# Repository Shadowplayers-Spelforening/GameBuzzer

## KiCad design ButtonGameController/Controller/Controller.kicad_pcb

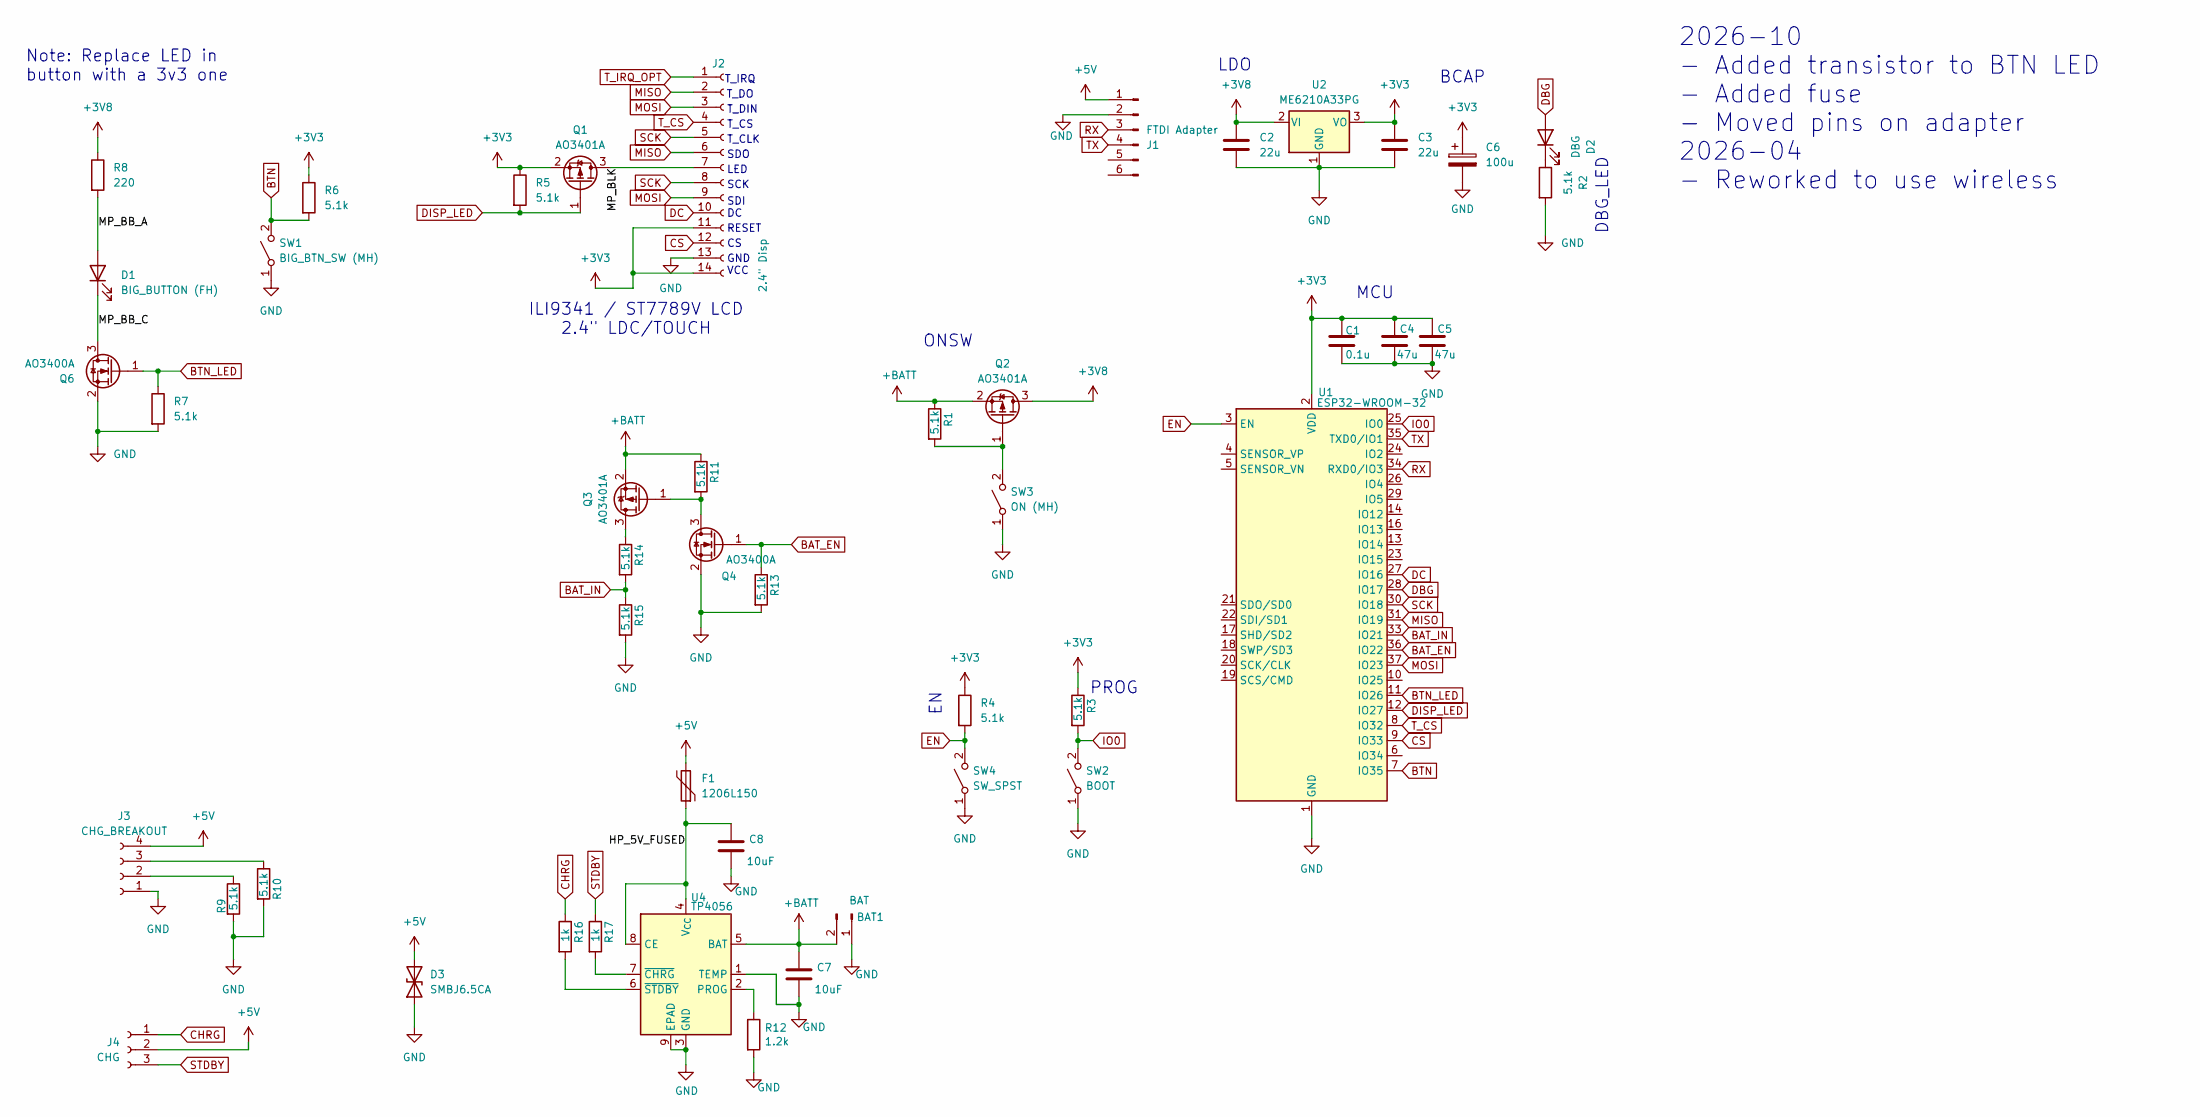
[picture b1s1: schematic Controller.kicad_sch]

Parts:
BAT1: BAT; PinSocket_1x02_P2.54mm_Vertical
C1: 0.1u; C_0603_1608Metric
C2, C3: 22u; C_0805_2012Metric
C4, C5: 47u; C_1206_3216Metric
C6: 100u; CP_Elec_5x5.4
C7, C8: 10uF; C_0805_2012Metric; LCSC C15850
D1: BIG_BUTTON (FH); LED_D5.0mm
D2: DBG; LED_0805_2012Metric
D3: SMBJ6.5CA; D_SMB_Unidirectional
F1: 1206L150; Fuse_1206_3216Metric
J1: FTDI Adapter; PinSocket_1x06_P2.54mm_Horizontal
J2: 2.4" Disp; PinSocket_1x14_P2.54mm_Vertical
J3: CHG_BREAKOUT; JST_PH_B4B-PH-K_1x04_P2.00mm_Vertical
J4: CHG; PinSocket_1x03_P2.54mm_Vertical
Q1, Q2, Q3: AO3401A; SOT-23
Q4, Q6: AO3400A; SOT-23
R1, R2, R3, R4, R5, R6, R7, R9, R10, R11, R13, R14, R15: 5.1k; R_0603_1608Metric
R8: 220; R_0805_2012Metric
R12: 1.2k; R_0603_1608Metric; LCSC C4177
R16, R17: 1k; R_0603_1608Metric
SW1: BIG_BTN_SW (MH); PinSocket_1x02_P2.54mm_Vertical
SW2: BOOT; SW_SPST_CK_RS282G05A3
SW3: ON (MH); PinHeader_1x02_P2.54mm_Vertical
SW4: SW_SPST; SW_SPST_CK_RS282G05A3
U1: ESP32-WROOM-32
U2: ME6210A33PG; SOT-89-3
U4: TP4056; SOIC-8-1EP_3.9x4.9mm_P1.27mm_EP2.41x3.3mm_ThermalVias; LCSC C725790

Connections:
+3V3: C1.1, C3.2, C4.1, C5.1, C6.1, J2.11, J2.14, Q1.2 (S), R3.1, R4.1, R5.1, R6.1, U1.2 (VDD), U2.3 (VO)
+3V8: C2.2, Q2.3 (D), R8.1, U2.2 (VI)
+5V: D3.2 (A2), F1.2, J1.1, J3.4, J4.2
+BATT: BAT1.2, C7.1, Q2.2 (S), Q3.2 (S), R1.1, R11.1, U4.5 (BAT)
/HP_5V_FUSED: C8.1, F1.1, U4.4 (V_{CC}), U4.8 (CE)
/MP_BB_A: D1.2 (A), R8.2
/MP_BB_C: D1.1 (K), Q6.3 (D)
/MP_BLK: J2.7, Q1.3 (D)
BAT_EN: Q4.1 (G), R13.1, U1.36 (IO22)
BAT_IN: R14.2, R15.1, U1.33 (IO21)
BTN: R6.2, SW1.2 (B), U1.7 (IO35)
BTN_LED: Q6.1 (G), R7.1, U1.11 (IO26)
CHRG: J4.1, R16.1
CS: J2.12, U1.9 (IO33)
DBG: D2.2 (A), U1.28 (IO17)
DC: J2.10, U1.27 (IO16)
DISP_LED: Q1.1 (G), R5.2, U1.12 (IO27)
EN: R4.2, SW4.2 (B), U1.3 (EN)
GND: BAT1.1, C1.2, C2.1, C3.1, C4.2, C5.2, C6.2, C7.2, C8.2, D3.1 (A1), J1.2, J2.13, J3.1, Q4.2 (S), Q6.2 (S), R2.2, R7.2, R9.2, R10.2, R12.2, R13.2, R15.2, SW1.1 (A), SW2.1 (A), SW3.1 (A), SW4.1 (A), U1.1 (GND), U1.15 (GND), U1.38 (GND), U1.39 (GND), U2.1 (GND), U4.1 (TEMP), U4.3 (GND), U4.9 (EPAD)
IO0: R3.2, SW2.2 (B), U1.25 (IO0)
MISO: J2.2, J2.6, U1.31 (IO19)
MOSI: J2.3, J2.9, U1.37 (IO23)
unnamed: D2.1 (K), R2.1
unnamed: J3.2, R9.1
unnamed: J3.3, R10.1
unnamed: Q2.1 (G), R1.2, SW3.2 (B)
unnamed: Q3.3 (D), R14.1
unnamed: Q3.1 (G), Q4.3 (D), R11.2
unnamed: R12.1, U4.2 (PROG)
unnamed: R17.2, U4.7 (~CHRG)
unnamed: R16.2, U4.6 (~STDBY)
RX: J1.3, U1.34 (RXD0/IO3)
SCK: J2.5, J2.8, U1.30 (IO18)
STDBY: J4.3, R17.1
TX: J1.4, U1.35 (TXD0/IO1)
T_CS: J2.4, U1.8 (IO32)
T_IRQ_OPT: J2.1

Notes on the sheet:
T_CS
PROG
VCC
LED
DBG_LED
GND
T_IRQ
MCU
ILI9341 / ST7789V LCD 2.4" LDC/TOUCH
T_CLK
LDO
Note: Replace LED in button with a 3v3 one
ONSW
T_DIN
BCAP
RESET
T_DO
SCK
SDI
2026-10 - Added transistor to BTN LED - Added fuse - Moved pins on adapter 2026-04 - Reworked to use wireless
SDO

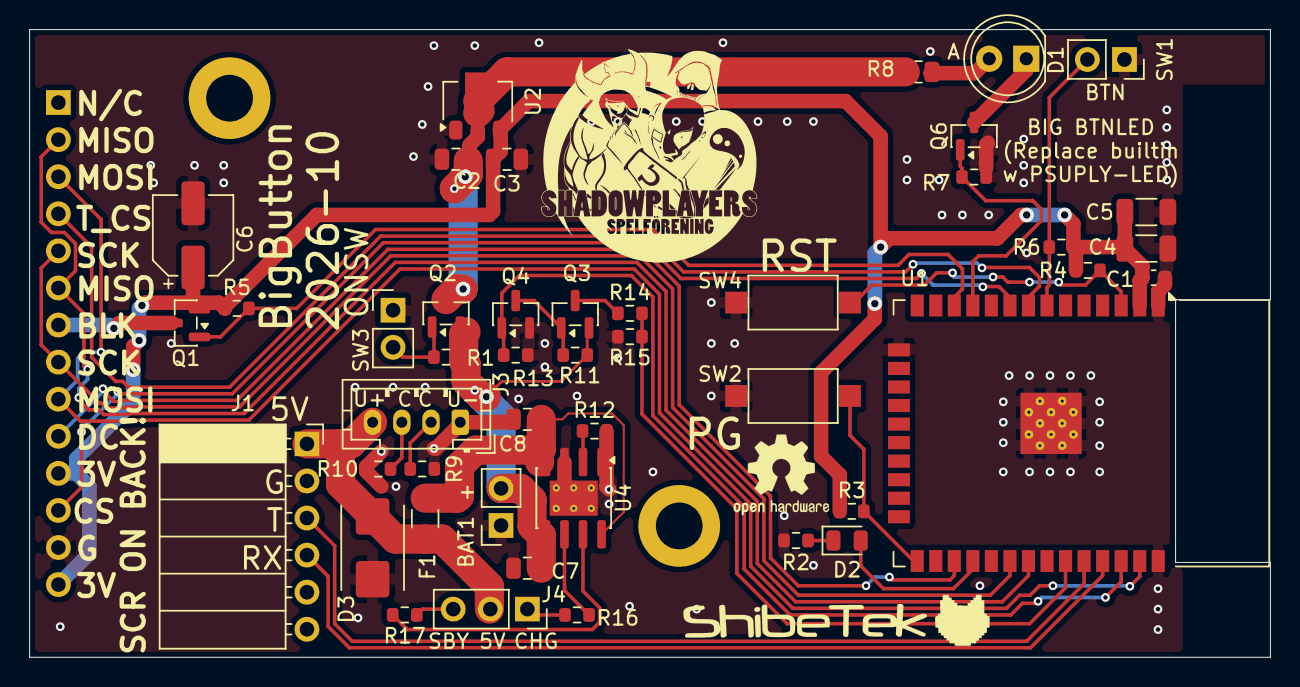
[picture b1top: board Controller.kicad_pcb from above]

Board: 2 copper layers, 85.0 x 43.0 mm, 46 parts (1 on the bottom side), 36 nets.

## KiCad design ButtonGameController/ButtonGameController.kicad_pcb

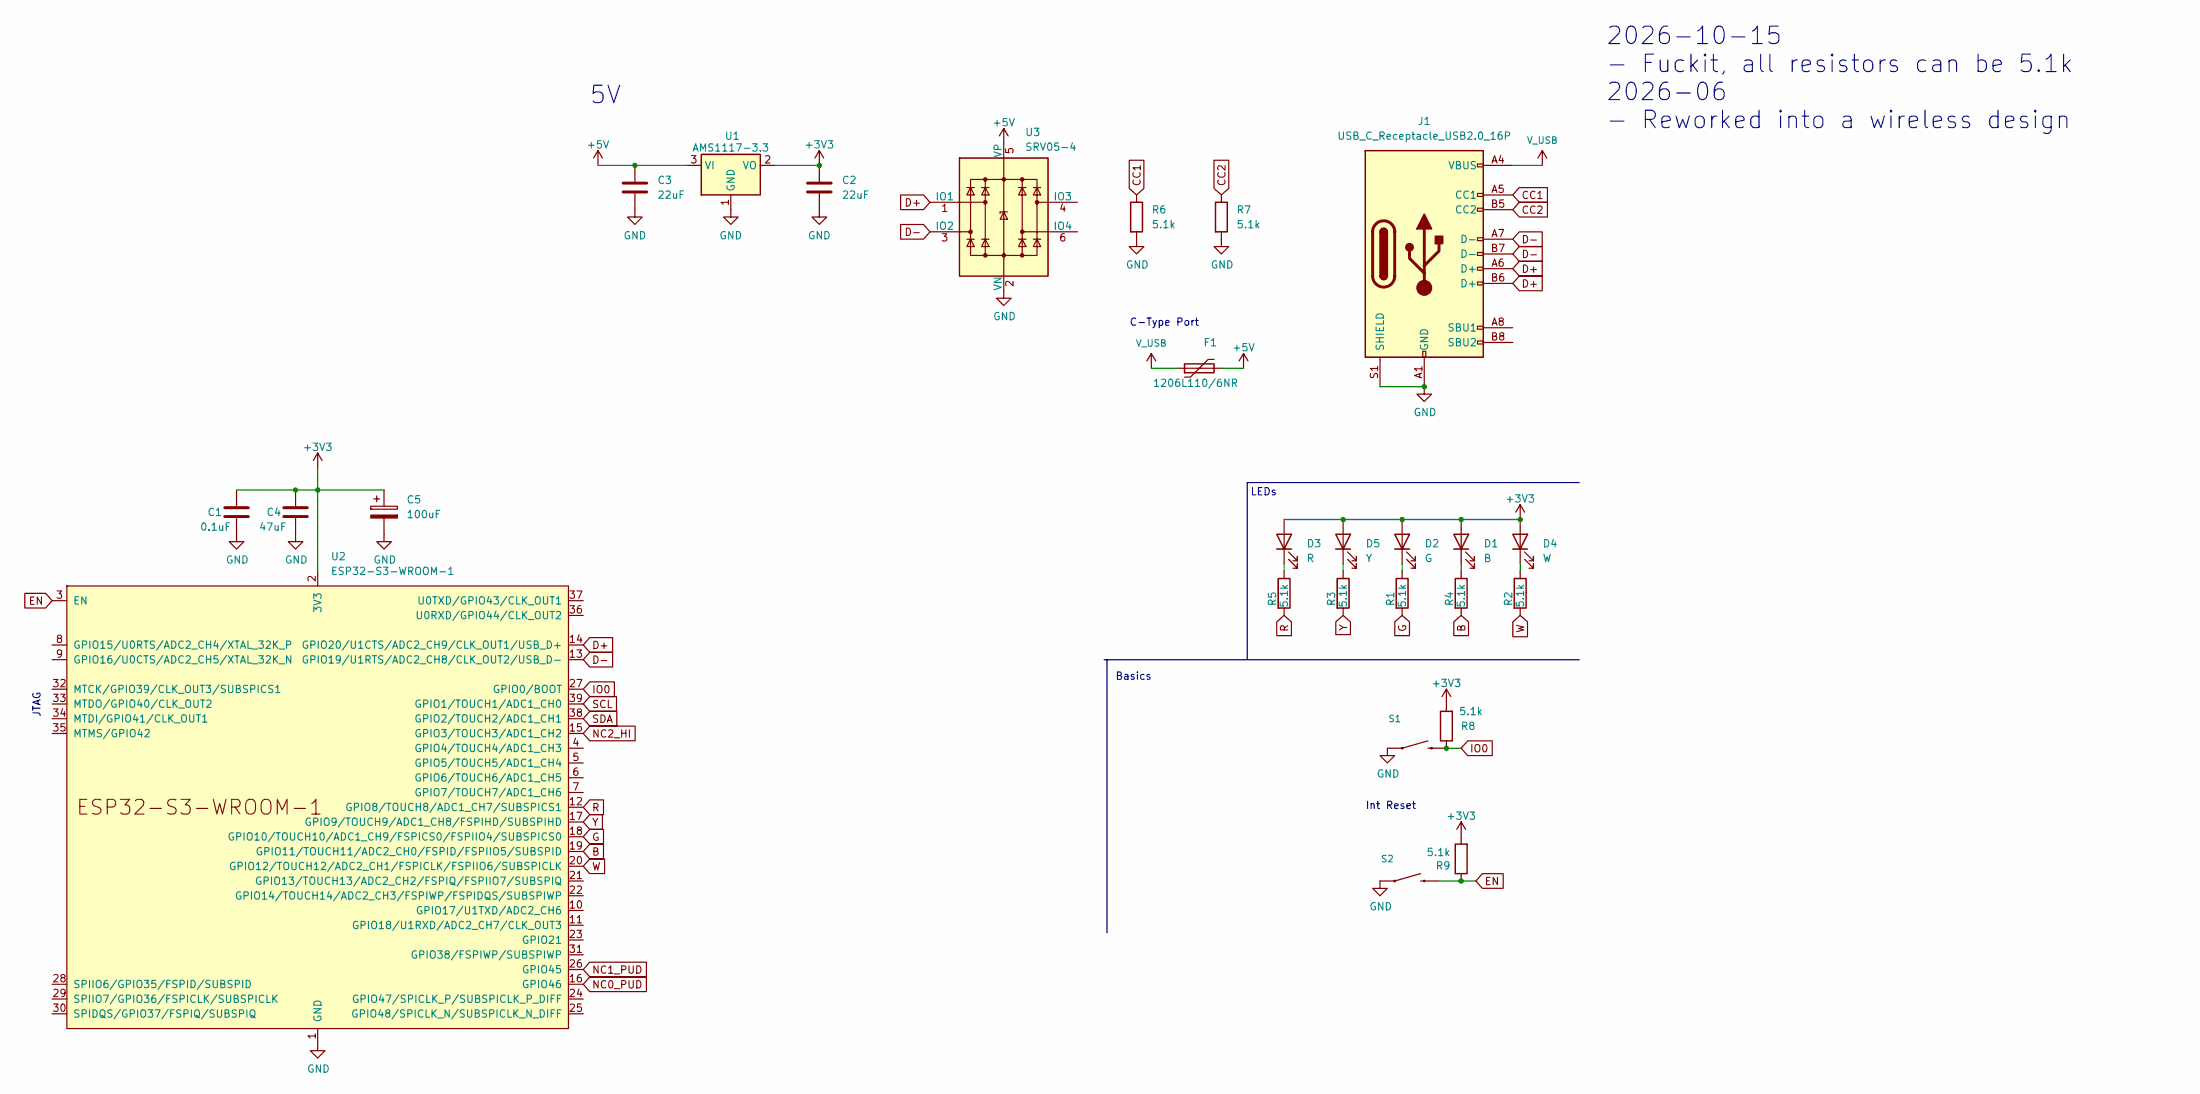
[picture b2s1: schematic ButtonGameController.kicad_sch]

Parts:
C1: 0.1uF; C_0603_1608Metric
C2, C3: 22uF; C_0805_2012Metric
C4: 47uF; C_1206_3216Metric
C5: 100uF; CP_Elec_5x4.5
D1: B; LED_D5.0mm
D2: G; LED_D5.0mm
D3: R; LED_D5.0mm
D4: W; LED_D5.0mm
D5: Y; LED_D5.0mm
F1: 1206L110/6NR; Fuse_1206_3216Metric
J1: USB_C_Receptacle_USB2.0_16P; USB_C_Receptacle_GCT_USB4105-xx-A_16P_TopMnt_Horizontal
R1, R2, R3, R4, R5, R6, R7, R8, R9: 5.1k; R_0603_1608Metric
S1: BOOT; SW_Tactile_SPST_NO_Straight_CK_PTS636Sx25SMTRLFS
S2: RST; SW_Tactile_SPST_NO_Straight_CK_PTS636Sx25SMTRLFS
U1: AMS1117-3.3; SOT-223-3_TabPin2
U2: ESP32-S3-WROOM-1
U3: SRV05-4; SOT-23-6

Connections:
+3V3: C1.1, C2.1, C4.1, C5.1, D1.2 (A), D2.2 (A), D3.2 (A), D4.2 (A), D5.2 (A), R8.2, R9.2, U1.2 (VO), U2.2 (3V3)
+5V: C3.1, F1.2, U1.3 (VI), U3.5 (VP)
B: R4.2, U2.19 (GPIO11/TOUCH11/ADC2_CH0/FSPID/FSPIIO5/S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)
CC1: J1.A5 (CC1), R6.1
CC2: J1.B5 (CC2), R7.1
D+: J1.A6 (D+), J1.B6 (D+), U2.14 (GPIO20/U1CTS/ADC2_CH9/CLK_OUT1/USB_D+), U3.1 (IO1)
D-: J1.A7 (D-), J1.B7 (D-), U2.13 (GPIO19/U1RTS/ADC2_CH8/CLK_OUT2/USB_D-), U3.3 (IO2)
EN: R9.1, S2.2, U2.3 (EN)
G: R1.2, U2.18 (GPIO10/TOUCH10/ADC1_CH9/FSPICS0/FSPIIO4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)
GND: C1.2, C2.2, C3.2, C4.2, C5.2, J1.A1 (GND), J1.A12 (GND), J1.B1 (GND), J1.B12 (GND), J1.S1 (SHIELD), R6.2, R7.2, S1.1, S2.1, U1.1 (GND), U2.1 (GND), U2.40 (GND), U2.41 (GND), U3.2 (VN)
IO0: R8.1, S1.2, U2.27 (GPIO0/BOOT)
NC0_PUD: U2.16 (GPIO46)
NC1_PUD: U2.26 (GPIO45)
NC2_HI: U2.15 (GPIO3/TOUCH3/ADC1_CH2)
unnamed: D1.1 (K), R4.1
unnamed: D2.1 (K), R1.1
unnamed: D3.1 (K), R5.1
unnamed: D4.1 (K), R2.1
unnamed: D5.1 (K), R3.1
R: R5.2, U2.12 (GPIO8/TOUCH8/ADC1_CH7/SUBSPICS1)
SCL: U2.39 (GPIO1/TOUCH1/ADC1_CH0)
SDA: U2.38 (GPIO2/TOUCH2/ADC1_CH1)
V_USB: F1.1, J1.A4 (VBUS), J1.A9 (VBUS), J1.B4 (VBUS), J1.B9 (VBUS)
W: R2.2, U2.20 (GPIO12/TOUCH12/ADC2_CH1/FSPICLK/FSPIIO6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)
Y: R3.2, U2.17 (GPIO9/TOUCH9/ADC1_CH8/FSPIHD/SUBSPIHD)

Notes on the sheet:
LEDs
C-Type Port
2026-10-15 - Fuckit, all resistors can be 5.1k 2026-06 - Reworked into a wireless design
Int Reset
JTAG
Basics

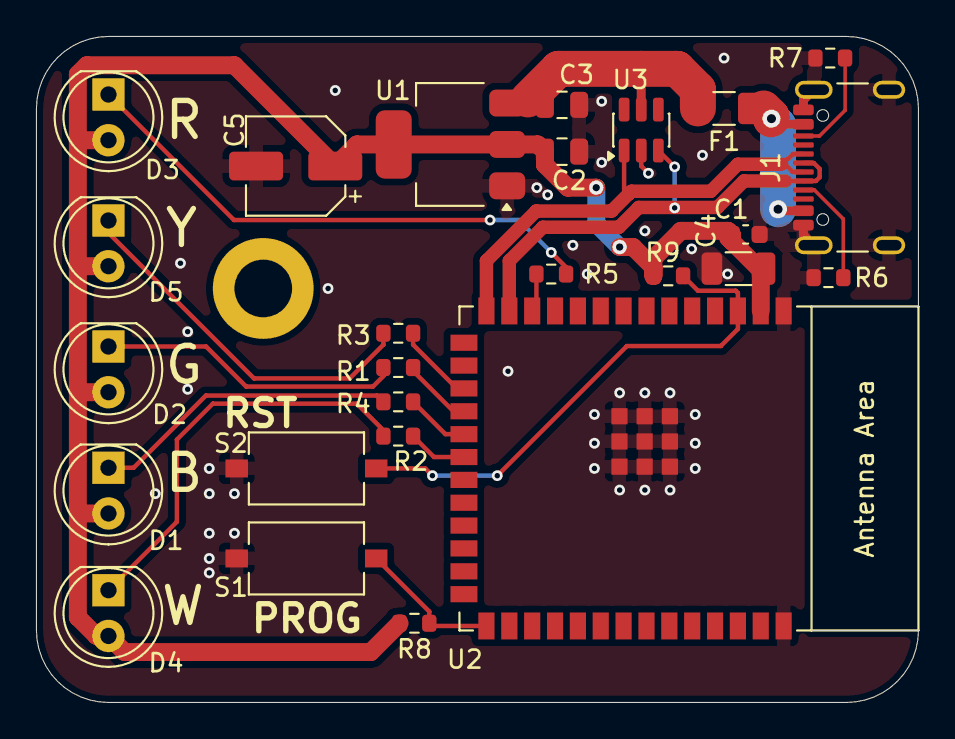
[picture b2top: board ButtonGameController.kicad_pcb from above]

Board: 2 copper layers, 49.0 x 37.0 mm, 26 parts (0 on the bottom side), 20 nets.

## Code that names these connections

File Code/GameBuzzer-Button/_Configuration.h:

#pragma once
#include <arduino.h>
#include "Shared.h"

// note: because the screen is mounted upside down, these get flipped 
struct DisplayCalibration{
	uint16_t top;			// high X (bottom in the real world)
	uint16_t bottom;		// low X (top in the real world
	uint16_t left;			// low Y (right in the real world)
	uint16_t right;			// high Y (left in the real world)
};

namespace Configuration{

	const size_t NUM_BUTTONS = 5;

	//const ButtonColor myColor = RED;
	const ButtonColor myColor = YELLOW;
	//const ButtonColor myColor = GREEN;
	//const ButtonColor myColor = BLUE;
	//const ButtonColor myColor = WHITE;

	const DisplayCalibration displayCalibration[NUM_BUTTONS] = {
		{3775,414,691,3604}, // Red
		{3799,291,752,3657}, // yellow
		{3826,433,577,3448}, // green
		{3627,587,343,3770}, // blue
		{3754,532,377,3738}, // white
	};




	const uint16_t TOUCH_TOP = displayCalibration[myColor].top;    
	const uint16_t TOUCH_BOTTOM = displayCalibration[myColor].bottom;
	const uint16_t TOUCH_LEFT = displayCalibration[myColor].left;
	const uint16_t TOUCH_RIGHT = displayCalibration[myColor].right;

	const bool INVERT_SCREEN = true;

	const uint8_t PIN_DC = 16;
	const uint8_t PIN_DBG_LED = 17;
	const uint8_t PIN_BTN_LED = 26;
	const uint8_t PIN_DISP_LED = 27;
	const uint8_t PIN_T_CS = 32;
	const uint8_t PIN_CS = 33;
	const uint8_t PIN_BTN = 35;

	

};
